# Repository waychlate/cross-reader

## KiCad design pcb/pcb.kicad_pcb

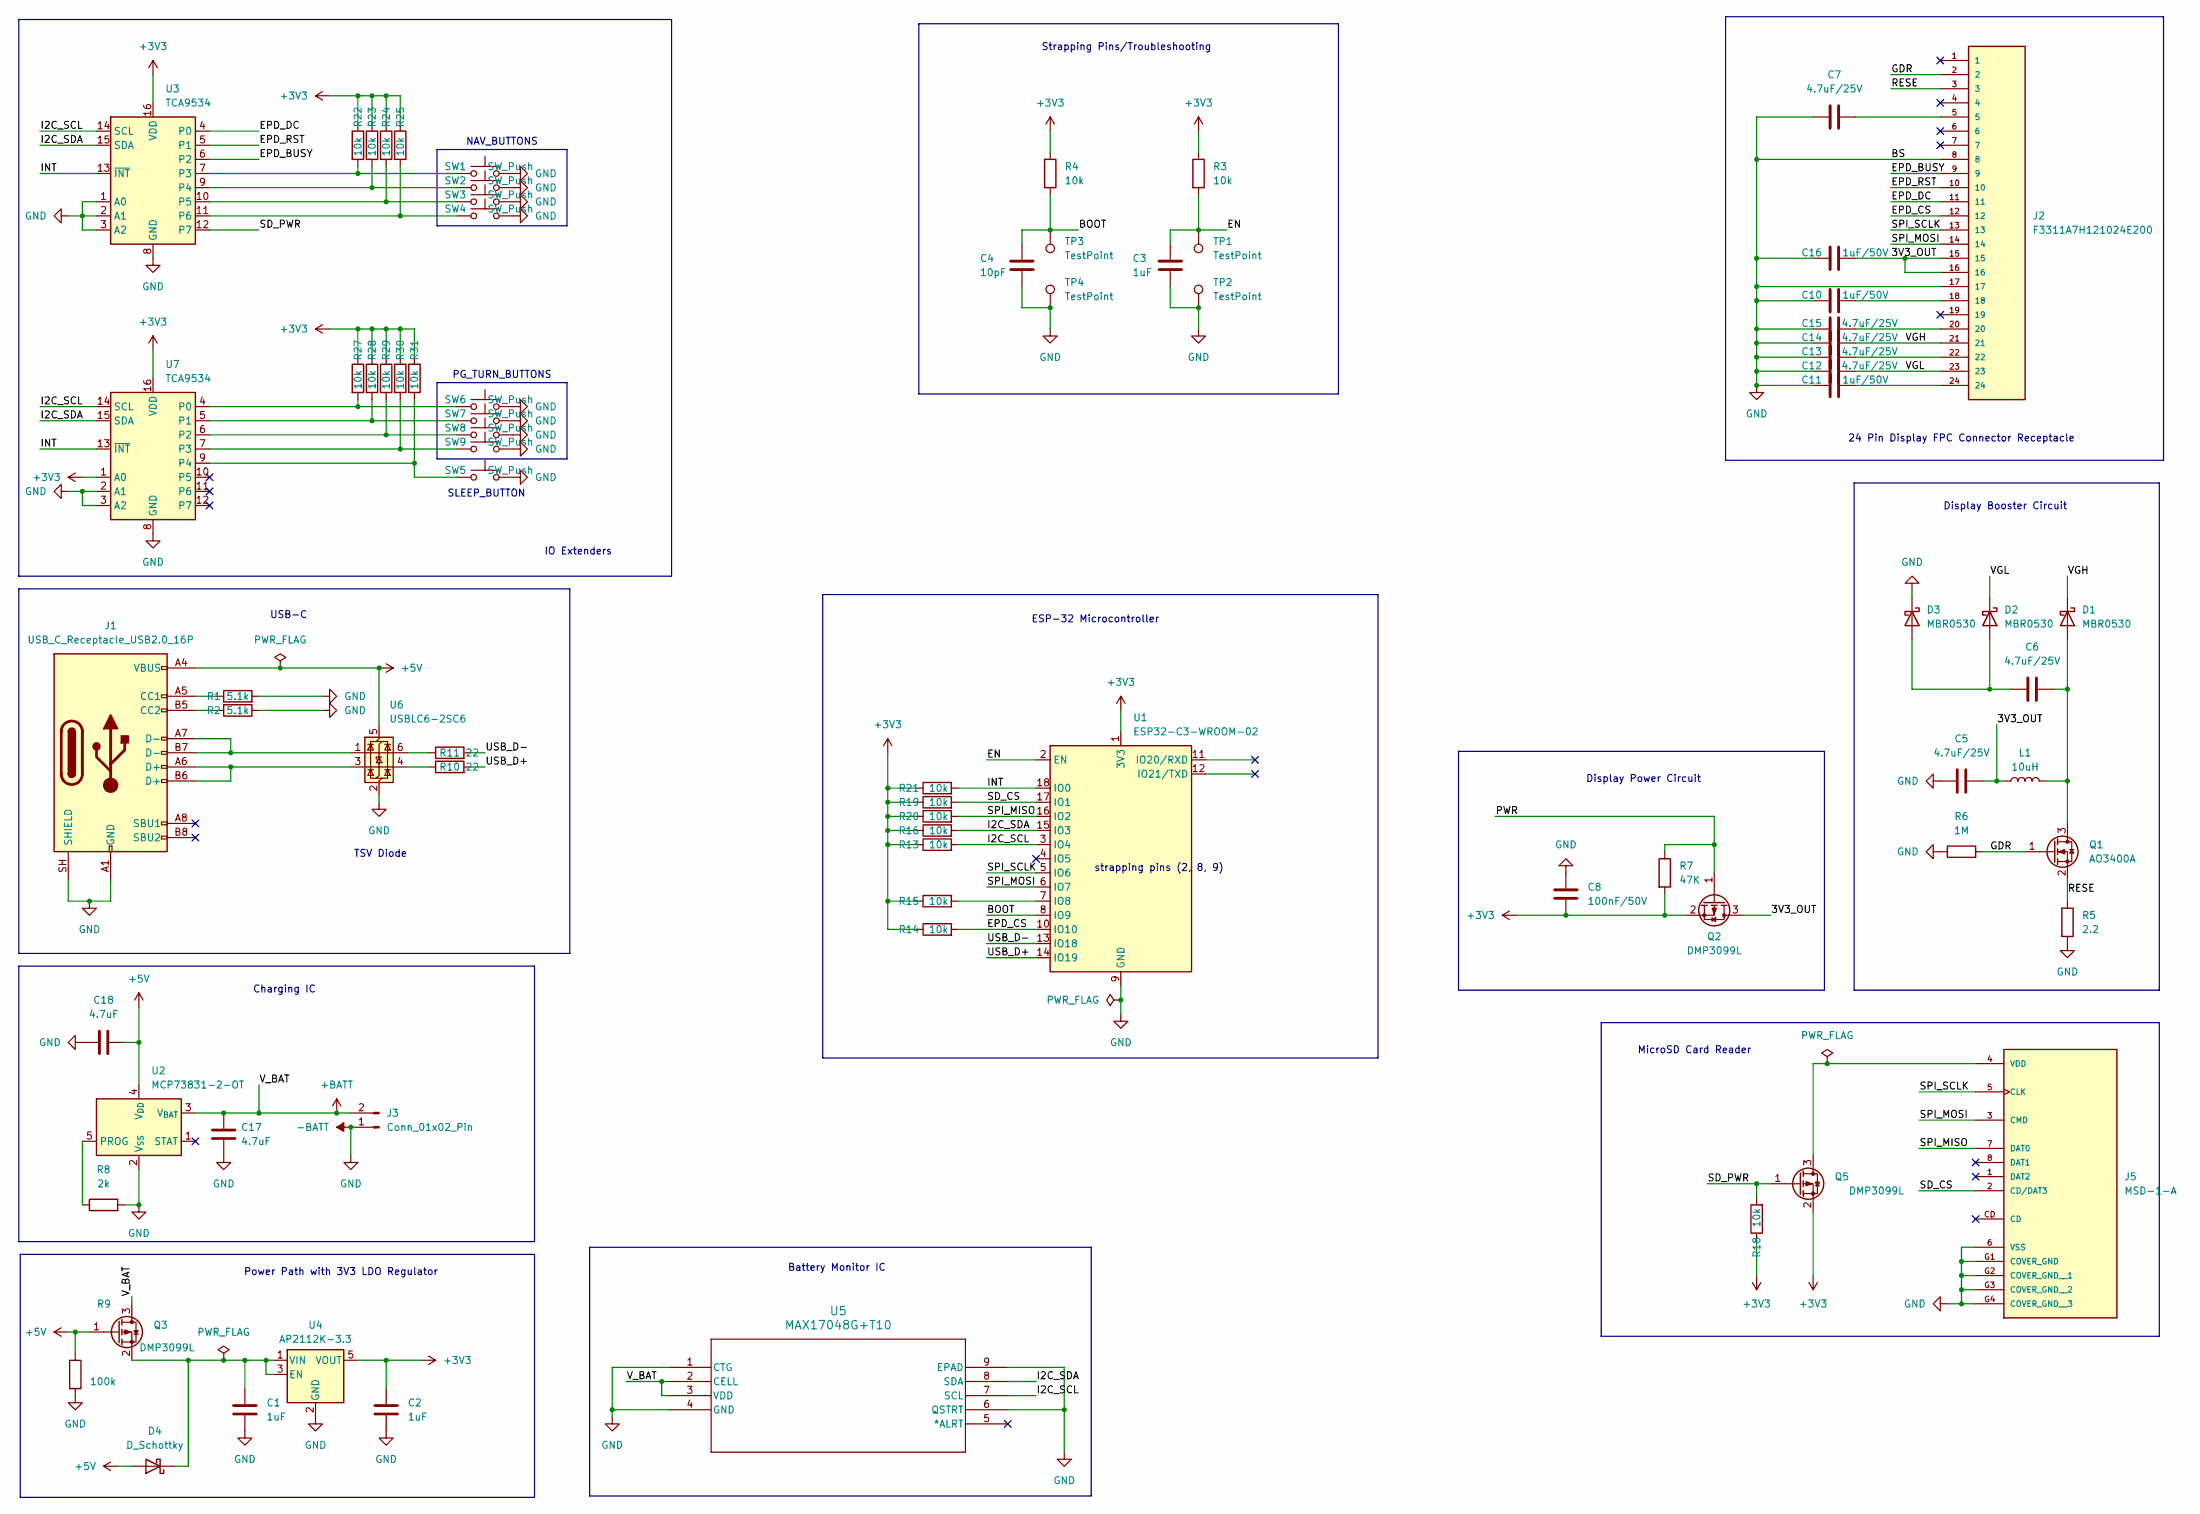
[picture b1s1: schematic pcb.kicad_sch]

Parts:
C1, C2, C3: 1uF; C_0805_2012Metric_Pad1.18x1.45mm_HandSolder
C4: 10pF; C_0805_2012Metric_Pad1.18x1.45mm_HandSolder
C5, C6, C7, C12, C13, C14, C15: 4.7uF/25V; C_0805_2012Metric_Pad1.18x1.45mm_HandSolder
C8: 100nF/50V; C_0805_2012Metric_Pad1.18x1.45mm_HandSolder
C10, C11, C16: 1uF/50V; C_0805_2012Metric_Pad1.18x1.45mm_HandSolder
C17, C18: 4.7uF; C_0805_2012Metric_Pad1.18x1.45mm_HandSolder
D1, D2, D3: MBR0530; D_SOD-123
D4: D_Schottky; D_SOD-123
J1: USB_C_Receptacle_USB2.0_16P; USB_C_Receptacle_GCT_USB4105-xx-A_16P_TopMnt_Horizontal
J2: F3311A7H121024E200; AMPHENOL_F3311A7H121024E200; PARTREV A
J3: Conn_01x02_Pin; JST_PH_B2B-PH-K_1x02_P2.00mm_Vertical
J5: MSD-1-A; CUI_MSD-1-A; PARTREV 1.0
L1: 10uH; L_Taiyo-Yuden_NR-24xx_HandSoldering
Q1: AO3400A; SOT-23
Q2, Q3, Q5: DMP3099L; SOT-23
R1, R2: 5.1k; R_0805_2012Metric_Pad1.20x1.40mm_HandSolder
R3, R4, R13, R14, R15, R16, R18, R19, R20, R21, R22, R23, R24, R25, R27, R28, R29, R30, R31: 10k; R_0805_2012Metric_Pad1.20x1.40mm_HandSolder
R5: 2.2; R_0805_2012Metric_Pad1.20x1.40mm_HandSolder
R6: 1M; R_0805_2012Metric_Pad1.20x1.40mm_HandSolder
R7: 47K; R_0805_2012Metric_Pad1.20x1.40mm_HandSolder
R8: 2k; R_0805_2012Metric_Pad1.20x1.40mm_HandSolder
R9: 100k; R_0805_2012Metric_Pad1.20x1.40mm_HandSolder
R10, R11: 22; R_0805_2012Metric_Pad1.20x1.40mm_HandSolder
SW1, SW2, SW3, SW4: SW_Push; SW_PUSH_6mm
SW5, SW6, SW7, SW8, SW9: SW_Push; SW_Tactile_SPST_Angled_PTS645Vx39-2LFS
TP1, TP2, TP3, TP4: TestPoint; TestPoint_Pad_D1.5mm
U1: ESP32-C3-WROOM-02
U2: MCP73831-2-OT; SOT-23-5
U3, U7: TCA9534; SOIC127P1030X265-16N
U4: AP2112K-3.3; SOT-23-5
U5: MAX17048G+T10; 21-0168E_T822-3_MXM-M
U6: USBLC6-2SC6; SOT-23-6

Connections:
+3V3: C2.1, C8.1, Q2.2 (S), Q5.2 (S), R3.1, R4.1, R7.2, R13.1, R14.1, R15.1, R16.1, R18.1, R19.1, R20.1, R21.1, R22.1, R23.1, R24.1, R25.1, R27.1, R28.1, R29.1, R30.1, R31.1, U1.1 (3V3), U3.16 (VDD), U4.5 (VOUT), U7.1 (A0), U7.16 (VDD)
+5V: C18.2, D4.2 (A), J1.A4 (VBUS), J1.A9 (VBUS), J1.B4 (VBUS), J1.B9 (VBUS), Q3.1 (G), R9.1, U2.4 (V_{DD}), U6.5 (VBUS)
+BATT: C17.1, J3.2, Q3.3 (D), U2.3 (V_{BAT}), U5.2 (CELL), U5.3 (VDD)
-BATT: C1.2, C2.2, C3.1, C4.1, C5.1, C7.1, C8.2, C10.1, C11.1, C12.1, C13.1, C14.1, C15.1, C16.1, C17.2, C18.1, D3.1 (K), J1.A1 (GND), J1.A12 (GND), J1.B1 (GND), J1.B12 (GND), J1.SH (SHIELD), J2.8, J2.17, J3.1, J5.6 (VSS), J5.G1 (COVER_GND), J5.G2 (COVER_GND__1), J5.G3 (COVER_GND__2), J5.G4 (COVER_GND__3), R1.2, R2.1, R5.2, R6.1, R8.2, R9.2, SW1.2, SW2.2, SW3.2, SW4.2, SW5.2, SW6.2, SW7.2, SW8.2, SW9.2, TP2.1 (1_1), TP4.1 (1_1), U1.9 (GND), U1.19 (GND), U2.2 (V_{SS}), U3.1 (A0), U3.2 (A1), U3.3 (A2), U3.8 (GND), U4.2 (GND), U5.1 (CTG), U5.4 (GND), U5.6 (QSTRT), U5.9 (EPAD), U6.2 (GND), U7.2 (A1), U7.3 (A2), U7.8 (GND)
/3V3_OUT: C5.2, C16.2, J2.15, J2.16, L1.1, Q2.3 (D)
/BOOT: C4.2, R4.2, TP3.1 (1_1), U1.8 (IO9)
/EN: C3.2, R3.2, TP1.1 (1_1), U1.2 (EN)
/EPD_BUSY: J2.9, U3.6 (P2)
/EPD_CS: J2.12, R14.2, U1.10 (IO10)
/EPD_DC: J2.11, U3.4 (P0)
/EPD_RST: J2.10, U3.5 (P1)
/GDR: J2.2, Q1.1 (G), R6.2
/I2C_SCL: R13.2, U1.3 (IO4), U3.14 (SCL), U5.7 (SCL), U7.14 (SCL)
/I2C_SDA: R16.2, U1.15 (IO3), U3.15 (SDA), U5.8 (SDA), U7.15 (SDA)
/INT: R21.2, U1.18 (IO0), U3.13 (~INT), U7.13 (~INT)
/PWR: Q2.1 (G), R7.1
/RESE: J2.3, Q1.2 (S), R5.1
/SD_CS: J5.2 (CD/DAT3), R19.2, U1.17 (IO1)
/SD_PWR: Q5.1 (G), R18.2, U3.12 (P7)
/SPI_MISO: J5.7 (DAT0), R20.2, U1.16 (IO2)
/SPI_MOSI: J2.14, J5.3 (CMD), U1.6 (IO7)
/SPI_SCLK: J2.13, J5.5 (CLK), U1.5 (IO6)
/USB_D+: R10.2, U1.14 (IO19)
/USB_D-: R11.2, U1.13 (IO18)
/VGH: C14.2, D1.1 (K), J2.21
/VGL: C12.2, D2.1 (K), J2.23
unnamed: C7.2, J2.5
unnamed: C10.2, J2.18
unnamed: C11.2, J2.24
unnamed: C13.2, J2.22
unnamed: C15.2, J2.20
unnamed: C6.2, D1.2 (A), L1.2, Q1.3 (D)
unnamed: C6.1, D2.2 (A), D3.2 (A)
unnamed: C1.1, D4.1 (K), Q3.2 (S), U4.1 (VIN), U4.3 (EN)
unnamed: J1.A5 (CC1), R1.1
unnamed: J1.B5 (CC2), R2.2
unnamed: J1.A6 (D+), J1.B6 (D+), U6.3 (I/O2)
unnamed: J1.A7 (D-), J1.B7 (D-), U6.1 (I/O1)
unnamed: J5.4 (VDD), Q5.3 (D)
unnamed: R10.1, U6.4 (I/O2)
unnamed: R11.1, U6.6 (I/O1)
unnamed: R15.2, U1.7 (IO8)
unnamed: R8.1, U2.5 (PROG)
unnamed: R22.2, SW1.1, U3.7 (P3)
unnamed: R23.2, SW2.1, U3.9 (P4)
unnamed: R24.2, SW3.1, U3.10 (P5)
unnamed: R25.2, SW4.1, U3.11 (P6)
unnamed: R27.2, SW6.1, U7.4 (P0)
unnamed: R28.2, SW7.1, U7.5 (P1)
unnamed: R29.2, SW8.1, U7.6 (P2)
unnamed: R30.2, SW9.1, U7.7 (P3)
unnamed: R31.2, SW5.1, U7.9 (P4)

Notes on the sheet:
TSV Diode
Power Path with 3V3 LDO Regulator
PG_TURN_BUTTONS
Display Booster Circuit
Battery Monitor IC
NAV_BUTTONS
ESP-32 Microcontroller
MicroSD Card Reader
Charging IC
IO Extenders
Strapping Pins/Troubleshooting
Display Power Circuit
USB-C
strapping pins (2, 8, 9)
24 Pin Display FPC Connector Receptacle
SLEEP_BUTTON

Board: 4 copper layers, 78 parts (0 on the bottom side), 52 nets, no tracks yet.

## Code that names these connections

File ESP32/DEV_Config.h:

/*****************************************************************************
* | File      	:   DEV_Config.h
* | Author      :   Waveshare team
* | Function    :   Hardware underlying interface
* | Info        :
*----------------
* |	This version:   V1.0
* | Date        :   2020-02-19
* | Info        :
#
# Permission is hereby granted, free of charge, to any person obtaining a copy
# of this software and associated documnetation files (the "Software"), to deal
# in the Software without restriction, including without limitation the rights
# to use, copy, modify, merge, publish, distribute, sublicense, and/or sell
# copies of the Software, and to permit persons to  whom the Software is
# furished to do so, subject to the following conditions:
#
# The above copyright notice and this permission notice shall be included in
# all copies or substantial portions of the Software.
#
# THE SOFTWARE IS PROVIDED "AS IS", WITHOUT WARRANTY OF ANY KIND, EXPRESS OR
# IMPLIED, INCLUDING BUT NOT LIMITED TO THE WARRANTIES OF MERCHANTABILITY,
# FITNESS OR A PARTICULAR PURPOSE AND NONINFRINGEMENT. IN NO EVENT SHALL THE
# AUTHORS OR COPYRIGHT HOLDERS BE LIABLE FOR ANY CLAIM, DAMAGES OR OTHER
# LIABILITY WHETHER IN AN ACTION OF CONTRACT, TORT OR OTHERWISE, ARISING FROM,
# OUT OF OR IN CONNECTION WITH THE SOFTWARE OR THE USE OR OTHER DEALINGS IN
# THE SOFTWARE.
#
******************************************************************************/
#ifndef _DEV_CONFIG_H_
#define _DEV_CONFIG_H_

#include <Arduino.h>
#include <stdint.h>
#include <stdio.h>



/**
 * data
**/
#define UBYTE   uint8_t
#define UWORD   uint16_t
#define UDOUBLE uint32_t

/**
 * GPIO config
**/
#define EPD_SCK_PIN     8    // Hardware SPI SCK (D8)
#define EPD_MOSI_PIN    10   // Hardware SPI MOSI (D10)
#define EPD_CS_PIN      20   // Chip Select (D7 / GPIO20)
#define EPD_RST_PIN     4    // Reset (D2 / GPIO4)
#define EPD_DC_PIN      5    // Data/Command (D3 / GPIO5)
#define EPD_BUSY_PIN    3    // Busy Pin (D1 / GPIO3)
#define EPD_PWR_PIN     -1



#define GPIO_PIN_SET   1
#define GPIO_PIN_RESET 0

/**
 * GPIO read and write
**/
#define DEV_Digital_Write(_pin, _value) digitalWrite(_pin, _value == 0? LOW:HIGH)
#define DEV_Digital_Read(_pin) digitalRead(_pin)

/**
 * delay x ms
**/
#define DEV_Delay_ms(__xms) delay(__xms)

/*------------------------------------------------------------------------------------------------------*/
UBYTE DEV_Module_Init(void);
void GPIO_Mode(UWORD GPIO_Pin, UWORD Mode);
void DEV_SPI_WriteByte(UBYTE data);
UBYTE DEV_SPI_ReadByte();
void DEV_SPI_Write_nByte(UBYTE *pData, UDOUBLE len);
void DEV_Module_Exit(void);

#endif
